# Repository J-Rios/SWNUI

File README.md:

# SWNUI
Simple Wireless Natural User Interface (Final Degree Project)

Inside the world of electronics there is a large diversity of fields, from among all, in this Final Degree Project, we will focus in the ambit of the human-machine interaction.

We will proceed then, to perform the prototype of a simple natural user interface that is able to make a wireless communication with an extern system, in our case a PC. To do that, we will use a microcontroller based system that will process the acquired reads from an accelerometer and determines the gesture accomplished to transmit it later through a Bluetooth link to the reception system.

In that way, we will start by implementing the hardware design of the system, designing the electrical schematic and the CAD design of the printed circuit board (by using the Eagle software), manufacturing the board and doing the components solder process. Once completed the hardware of the system we will continue with the software design, at both side of the system: the prototype manufactured and the extern system (PC), that allows verify the correct functionality of the system.

Complementary to the hardware and software development, we will work out the 3D model of the prototype enclosure (by using the Freecad software).

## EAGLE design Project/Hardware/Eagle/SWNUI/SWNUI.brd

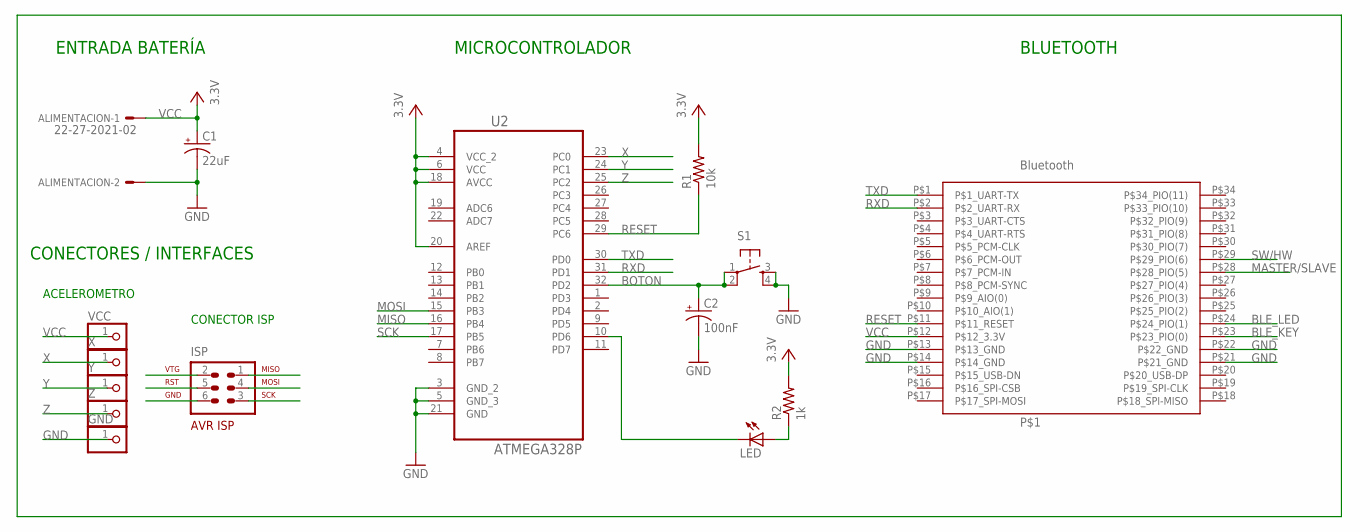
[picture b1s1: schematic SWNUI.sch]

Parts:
ALIMENTACION: 22-27-2021-02; 6410-02
C1: 22uF; EIA3216
C2: 100nF; EIA3216
GND: PINHD-1X1; 1X01
ISP: AVR-ISP-6
LED: LEDCHIP-LED0805; CHIP-LED0805
P$1: Bluetooth; BTM400
R1: 10k; 0805
R2: 1k; 0805
S1: TAC_SWITCHPTH; TACTILE-PTH
U2: ATMEGA328P; QFP80P900X900X120-32N
VCC: PINHD-1X1; 1X01
X: PINHD-1X1; 1X01
Y: PINHD-1X1; 1X01
Z: PINHD-1X1; 1X01

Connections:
BLE_KEY: P$1.P$23 (P$23_PIO(0))
BLE_LED: P$1.P$24 (P$24_PIO(1))
BOTON: C2.A (+), S1.1, S1.2, U2.32 (PD2)
GND: ALIMENTACION.2, C1.C (-), C2.C (-), GND.1, ISP.6, P$1.P$13 (P$13_GND), P$1.P$14 (P$14_GND), P$1.P$21 (P$21_GND), P$1.P$22 (P$22_GND), S1.3, S1.4, U2.3 (GND_2), U2.5 (GND_3), U2.21 (GND)
MASTER/SLAVE: P$1.P$28 (P$28_PIO(5))
MISO: ISP.1, U2.16 (PB4)
MOSI: ISP.4, U2.15 (PB3)
unnamed: LED.C, U2.10 (PD6)
unnamed: LED.A, R2.1
RESET: ISP.5, P$1.P$11 (P$11_RESET), R1.1, U2.29 (PC6)
RXD: P$1.P$2 (P$2_UART-RX), U2.31 (PD1)
SCK: ISP.3, U2.17 (PB5)
SW/HW: P$1.P$29 (P$29_PIO(6))
TXD: P$1.P$1 (P$1_UART-TX), U2.30 (PD0)
VCC: ALIMENTACION.1, C1.A (+), ISP.2, P$1.P$12 (P$12_3.3V), R1.2, R2.2, U2.4 (VCC_2), U2.6 (VCC), U2.18 (AVCC), U2.20 (AREF), VCC.1
X: U2.23 (PC0), X.1
Y: U2.24 (PC1), Y.1
Z: U2.25 (PC2), Z.1

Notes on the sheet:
CONECTOR ISP
ACELEROMETRO
MICROCONTROLADOR
ENTRADA BATERÍA
CONECTORES / INTERFACES
BLUETOOTH

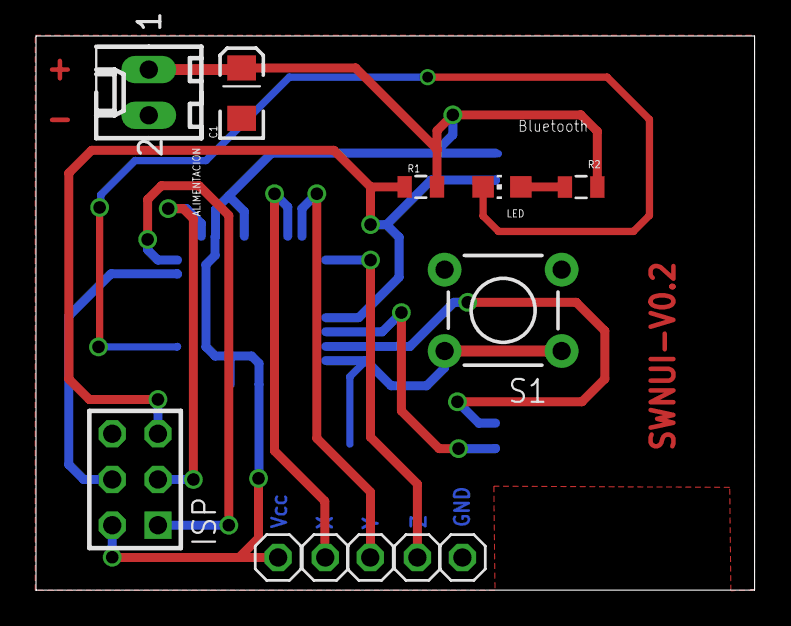
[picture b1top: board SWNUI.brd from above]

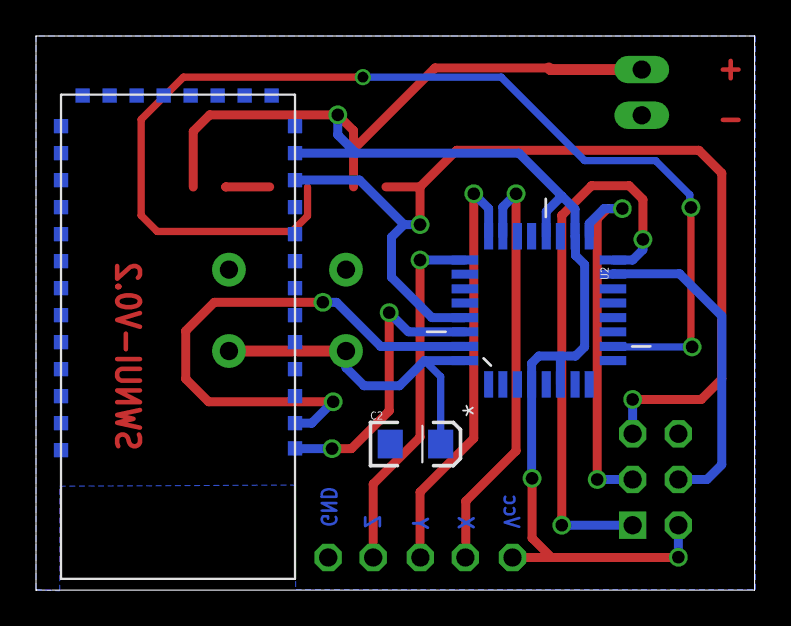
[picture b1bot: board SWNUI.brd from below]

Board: 2 copper layers, 39.9 x 30.8 mm, 15 parts (3 on the bottom side), 14 nets.

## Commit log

2015-07-26 Released version
    Released version 16/07/2015

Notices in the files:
parts and their libraries:
SparkFun-Capacitors: Licensing: Creative Commons ShareAlike 4.0 International - https://creativecommons.org/licenses/by-sa/4.0
